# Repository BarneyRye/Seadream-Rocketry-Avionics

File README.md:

# Seadream Rocketry PCB and Code
 
 | Kicad files include schematic, pcb, extra symbols, footprints 3d files and also the production files for JLCPCB |
 |---------|
 | Included code written in Platform.io on VSCode, uses prebuilt libaries and freeRTOS, one task for sensor reading and audio, other task for writing to SD |

 *Exclaimer: Component libraries only usable on KiCAD 9!* </br></br>

 Follow us on [Instagram](https://www.instagram.com/seadreamrocketry/)

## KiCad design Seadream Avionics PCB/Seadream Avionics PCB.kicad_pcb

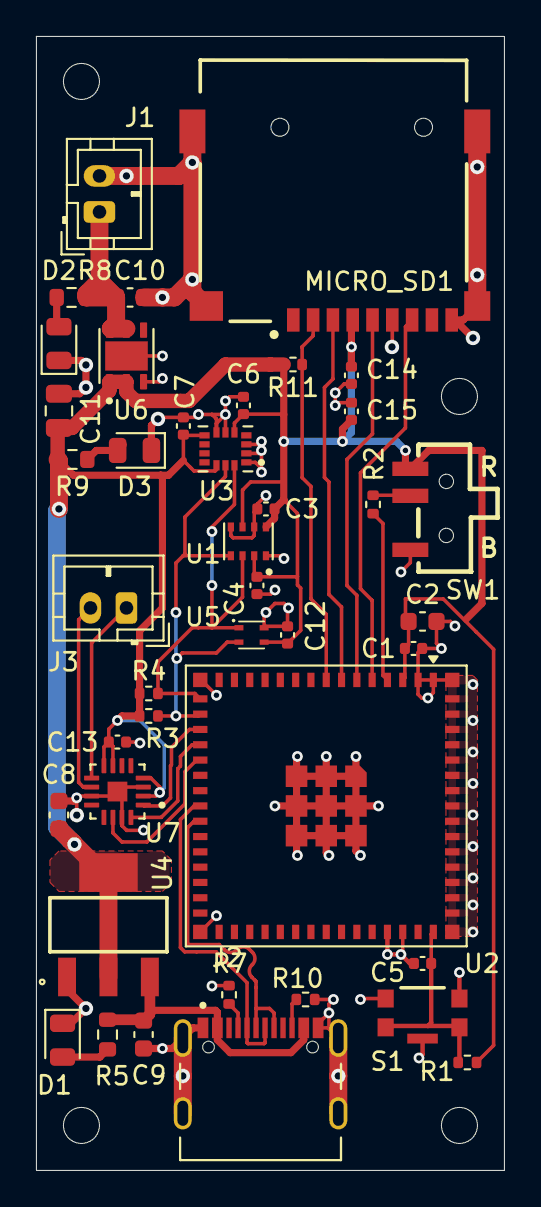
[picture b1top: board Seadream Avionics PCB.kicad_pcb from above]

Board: 2 copper layers, 26.0 x 63.0 mm, 41 parts (0 on the bottom side), 25 nets.

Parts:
C1, C3, C4, C5, C6, C7, C12, C13, C14: 100nF; C_0402_1005Metric
C2, C8, C9, C10: 10uF; C_0603_1608Metric
C11: 22uF; C_0805_2012Metric
C15: 1uF; C_0402_1005Metric
D1, D2, D3: LED; LED_0805_2012Metric
J1, J3: B2B-PH-K-S(LF)(SN); JST_PH_B2B-PH-K_1x02_P2.00mm_Vertical
J2: TYPE-C16PIN; SHOUHAN_TYPE-C_16PIN_2MD__073_
MICRO_SD1: TF-01A
R1, R2, R11: 10k; R_0402_1005Metric
R3, R4: 4k7; R_0402_1005Metric
R5: 330; R_0603_1608Metric
R7, R10: 5k1; R_0402_1005Metric
R8, R9: 220; R_0603_1608Metric
S1: KMR221GLFS; SW_KMR221GLFS
SW1: SSSS810701; SW-SMD_SSSS810701
U1: BMP280; XDCR_BMP280
U2: ESP32-S3-MINI-1U-N8; ESP32-S2-MINI-1U
U3: LSM6DSO32TR; XDCR_LSM6DSO32TR
U4: LD1117S33TR; SOT230P700X180-4N
U5: SHT40-AD1B-R3; SHT4X
U6: LD39200PU33R; SON95P300X300X100-7N
U7: MAX98357AETE_T; QFN50P300X300X80-17N

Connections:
+3.3V: C1.2, C2.2, C3.1, C4.1, C6.1, C7.1, C8.1, C11.2, C12.1, C13.1, C14.2, C15.2, MICRO_SD1.4 (VDD), R1.2, R3.1, R4.1, R9.1, R11.1, SW1.3 (C), U1.2 (CSB), U1.6 (VDDIO), U1.8 (VDD), U2.3 (3V3), U3.5 (VDDIO), U3.8 (VDD), U3.12 (CS), U4.2 (OUT), U4.4 (OUT), U5.3 (VDD), U6.1 (OUT), U6.2 (SENSE), U7.2 (GAIN_SLOT), U7.4 (SD_MODE), U7.7 (VDD), U7.8 (VDD)
/BOOT: R2.2, U2.4 (IO0)
/CD: MICRO_SD1.2 (CD/DAT3), R11.2, U2.8 (IO4)
/D+: J2.A6 (DP1), J2.B6 (DP2), U2.24 (IO20)
/D-: J2.A7 (DN1), J2.B7 (DN2), U2.23 (IO19)
/EN: C5.2, R1.1, S1.1, S1.4, U2.45 (EN)
/IO12: R4.2, U1.3 (SDI), U2.16 (IO12), U3.14 (SDA), U5.1 (SDA)
/IO13: R3.2, U1.4 (SCK), U2.17 (IO13), U3.13 (SCL), U5.2 (SCL)
/IO14: U2.18 (IO14), U7.1 (DIN)
/IO15: U2.19 (IO15), U7.16 (BCLK)
/IO16: U2.20 (IO16), U7.14 (LRCLK)
/MISO: MICRO_SD1.7 (DAT0), U2.5 (IO1)
/MOSI: MICRO_SD1.3 (CMD), U2.7 (IO3)
/OUT+: J3.1, U7.9 (OUTP)
/OUT-: J3.2, U7.10 (OUTN)
/SCK: MICRO_SD1.5 (CLK), U2.6 (IO2)
/USB 5V: C9.1, J2.A4_B9 (VBUS_A), J2.B4_A9 (VBUS_B), R5.1, U4.3 (IN)
GND: C1.1, C2.1, C3.2, C4.2, C5.1, C6.2, C7.2, C8.2, C9.2, C10.1, C11.1, C12.2, C13.2, C14.1, C15.1, D1.1 (K), D2.1 (K), D3.1 (K), J1.2, J2.A1_B12 (GND_A), J2.B1_A12 (GND_B), J2.SH1 (SHIELD), J2.SH2 (SHIELD), J2.SH3 (SHIELD), J2.SH4 (SHIELD), MICRO_SD1.6 (VSS), MICRO_SD1.CD1 (CD), MICRO_SD1.MP1 (SHIELD), MICRO_SD1.MP2 (SHIELD), MICRO_SD1.MP3 (SHIELD), MICRO_SD1.MP4 (SHIELD), R7.1, R10.2, S1.2, S1.3, S1.5, SW1.1 (A), U1.1 (GND), U1.5 (SDO), U1.7 (GND), U2.1 (GND1), U2.2 (GND1), U2.42 (GND1), U2.43 (GND1), U2.46 (GND1), U2.47 (GND1), U2.48 (GND1), U2.49 (GND1), U2.50 (GND1), U2.51 (GND1), U2.52 (GND1), U2.53 (GND1), U2.54 (GND2), U2.55 (GND2), U2.56 (GND2), U2.57 (GND2), U2.58 (GND2), U2.59 (GND2), U2.60 (GND3), U2.62 (GND2), U2.63 (GND2), U2.64 (GND2), U2.65 (GND2), U3.1 (SDO/SA0), U3.2 (SDX), U3.3 (SCX), U3.6 (GND), U3.7 (GND), U4.1 (GND), U5.4 (VSS), U6.3 (GND), U6.7 (EXP), U7.3 (GND), U7.11 (GND), U7.15 (GND), U7.17 (EP)
unnamed: D1.2 (A), R5.2
unnamed: D2.2 (A), R8.2
unnamed: D3.2 (A), R9.2
unnamed: C10.2, J1.1, R8.1, U6.5 (EN), U6.6 (IN)
unnamed: J2.A5 (CC1), R7.2
unnamed: J2.B5 (CC2), R10.1
unnamed: R2.1, SW1.2 (B)

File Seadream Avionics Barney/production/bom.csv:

Designator,Footprint,Quantity,Value,LCSC Part #
"C1, C12, C13, C14, C3, C4, C5, C6, C7",0402,9,100nF,
"C10, C2, C8, C9",0603,4,10uF,
C11,0805,1,22uF,
C15,0402,1,1uF,
"D1, D2, D3",0805,3,LED,
"J1, J3",JST_PH_B2B-PH-K_1x02_P2.00mm_Vertical,2,B2B-PH-K-S(LF)(SN),
J2,SHOUHAN_TYPE-C_16PIN_2MD__073_,1,C393939,
MICRO_SD1,TF-01A,1,C91145,
"R1, R11, R2",0402,3,10k,
"R10, R7",0402,2,5k1,
"R3, R4",0402,2,4k7,
R5,0603,1,330,
"R8, R9",0603,2,220,
S1,SW_KMR221GLFS,1,KMR221GLFS,
SW1,SW-SMD_SSSS810701,1,SSSS810701,
U1,XDCR_BMP280,1,BMP280,
U2,ESP32-S2-MINI-1U,1,ESP32-S3-MINI-1U-N8,
U3,XDCR_LSM6DSO32TR,1,LSM6DSO32TR,
U4,SOT230P700X180-4N,1,LD1117S33TR,
U5,SHT4X,1,SHT40-AD1B-R3,
U6,SON95P300X300X100-7N,1,LD39200PU33R,
U7,QFN50P300X300X80-17N,1,MAX98357AETE_T,

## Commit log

2025-12-30 Added comments and moved some initial start times with millis
2026-01-12 Added takeoff detection
2026-01-12 Fixed issue with indexing in takeoff_detection function
2026-01-12 Altitude detection bug fix
2026-01-12 Bug Fixes
2026-01-14 Updated PCB files
2026-01-14 Corrected pin defines
2026-01-14 Schematic Update
2026-01-16 Quick Update
2026-01-18 Update README with project details and repository link
    Added additional details about the project and a link to the related repository for log file analysis.
2026-01-20 Added £D file of PCB
2026-01-20 Renamed Files
2026-01-26 Added SD reconnect and connection flags
2026-01-26 Quick edits
2026-01-26 Quick edit
2026-02-09 Changed reduce log rate to after apogee
2026-03-05 Revise README with new logging frequency details
    Updated README to reflect changes in logging frequency and formatting.
2026-04-22 Update README with compatibility note for KiCAD
    Added a note about component libraries compatibility.
2026-05-01 Update README with Instagram link and formatting
    Added Instagram link and adjusted formatting.
